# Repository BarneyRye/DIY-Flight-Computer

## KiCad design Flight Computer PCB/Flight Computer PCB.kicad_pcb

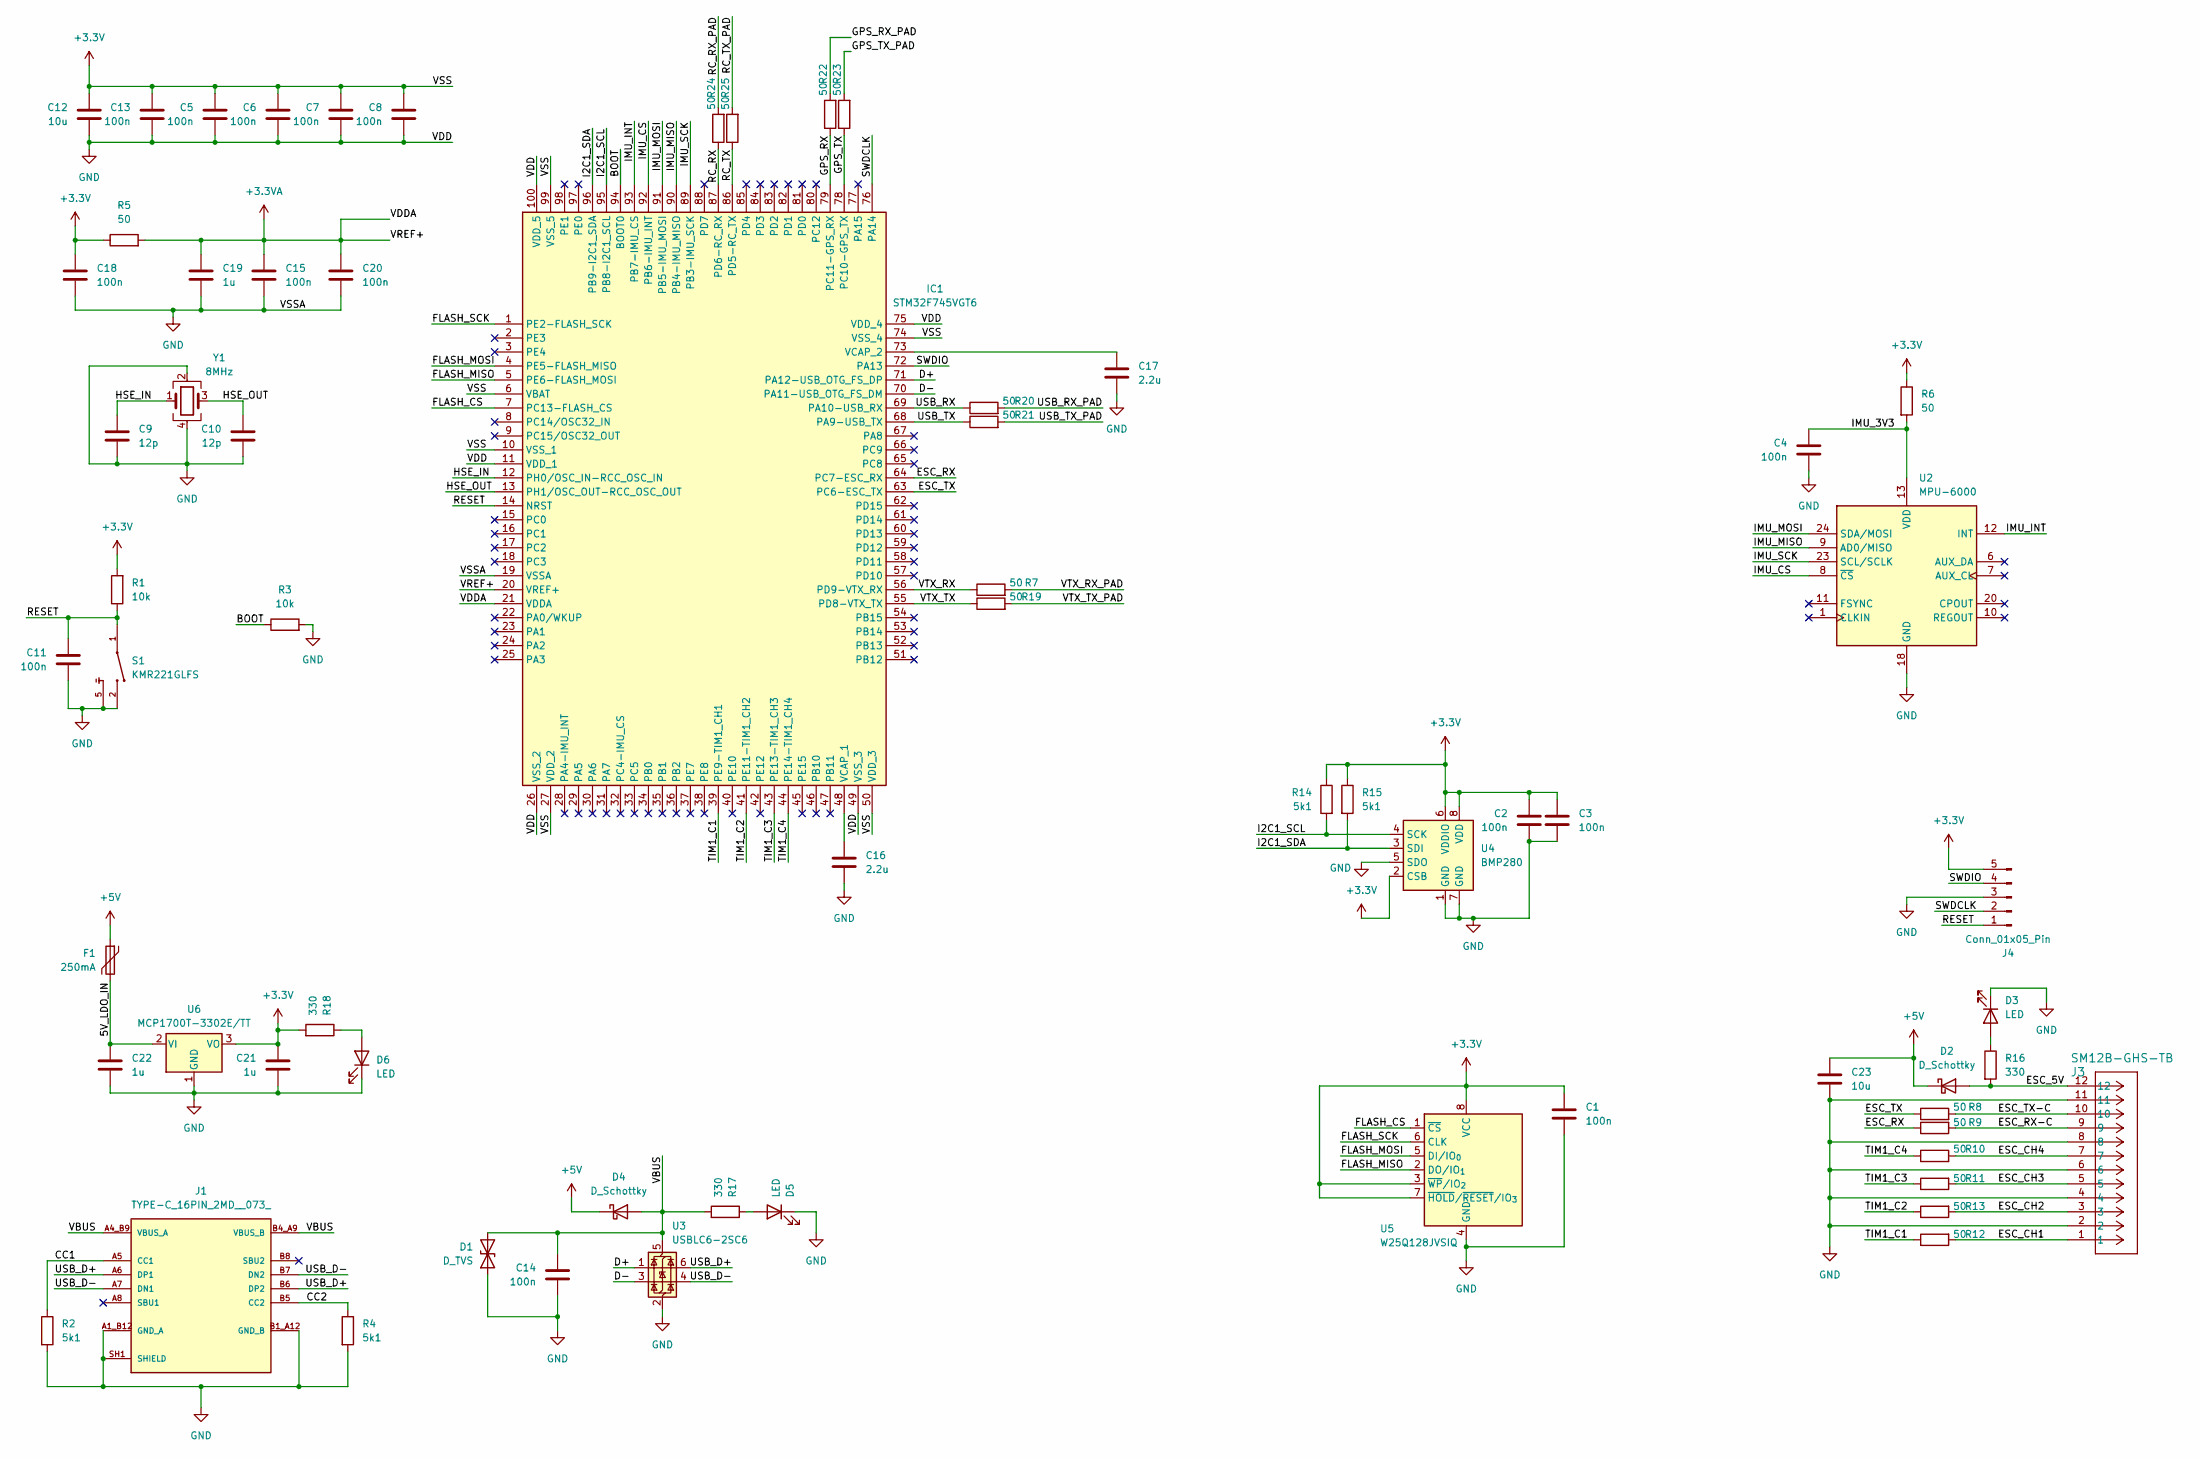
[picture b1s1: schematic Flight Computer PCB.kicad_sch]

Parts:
C1, C2, C3, C4, C5, C6, C7, C8, C11, C13, C14, C15, C18, C20: 100n; C_0805_2012Metric
C9, C10: 12p; C_0805_2012Metric
C12, C23: 10u; C_0805_2012Metric
C16, C17: 2.2u; C_0805_2012Metric
C19, C21, C22: 1u; C_0805_2012Metric
D1: D_TVS; C_0805_2012Metric
D2, D4: D_Schottky; C_0805_2012Metric
D3, D5, D6: LED; LED_0805_2012Metric
F1: 250mA; C_0805_2012Metric
IC1: STM32F745VGT6; QFP50P1600X1600X160-100N
J1: TYPE-C_16PIN_2MD__073_; SHOUHAN_TYPE-C_16PIN_2MD__073_; Part NO. C393939
J3: SM12B-GHS-TB; CONN_SM12B-GHS-TB_JST
J4: Conn_01x05_Pin; PinHeader_1x05_P2.54mm_Horizontal
R1, R3: 10k; R_0805_2012Metric
R2, R4, R14, R15: 5k1; R_0805_2012Metric
R5, R6, R7, R8, R9, R10, R11, R12, R13, R19, R20, R21, R22, R23, R24, R25: 50; R_0805_2012Metric
R16, R17, R18: 330; R_0805_2012Metric
S1: KMR221GLFS; SW_KMR221GLFS; Part NO. C72443
U2: MPU-6000; InvenSense_QFN-24_4x4mm_P0.5mm
U3: USBLC6-2SC6; SOT-23-6; Part NO. C7519
U4: BMP280; Bosch_LGA-8_2x2.5mm_P0.65mm_ClockwisePinNumbering
U5: W25Q128JVSIQ; SOIC-8_5.3x5.3mm_P1.27mm
U6: MCP1700T-3302E/TT; SOT-23
Y1: 8MHz; Crystal_SMD_3225-4Pin_3.2x2.5mm; Part NO. C70590

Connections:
+3.3V: C1.2, C2.2, C3.2, C5.1, C6.1, C7.1, C8.1, C12.1, C13.1, C18.2, C21.1, IC1.6 (VBAT), IC1.10 (VSS_1), IC1.27 (VDD_2), IC1.50 (VDD_3), IC1.74 (VSS_4), IC1.99 (VSS_5), J4.5, R1.2, R5.1, R6.1, R14.1, R15.1, R18.2, U4.2 (CSB), U4.6 (VDDIO), U4.8 (VDD), U5.3 (~WP/IO_{2}), U5.7 (~HOLD/~RESET/IO_{3}), U5.8 (VCC), U6.3 (VO)
+3.3VA: C15.2, C19.1, C20.2, IC1.20 (VREF+), IC1.21 (VDDA), R5.2
+5V: C23.1, D2.1 (K), D4.1 (K), F1.1
/5V_LDO_IN: C22.1, F1.2, U6.2 (VI)
/BOOT: IC1.94 (BOOT0), R3.1
/CC1: J1.A5 (CC1), R2.1
/CC2: J1.B5 (CC2), R4.1
/D+: IC1.71 (PA12-USB_OTG_FS_DP), U3.1 (I/O1)
/D-: IC1.70 (PA11-USB_OTG_FS_DM), U3.3 (I/O2)
/ESC_5V: D2.2 (A), J3.12, R16.2
/ESC_CH1: J3.1, R12.2
/ESC_CH2: J3.3, R13.2
/ESC_CH3: J3.5, R11.2
/ESC_CH4: J3.7, R10.2
/ESC_RX: IC1.64 (PC7-ESC_RX), R9.1
/ESC_RX-C: J3.9, R9.2
/ESC_TX: IC1.63 (PC6-ESC_TX), R8.1
/ESC_TX-C: J3.10, R8.2
/FLASH_CS: IC1.7 (PC13-FLASH_CS), U5.1 (~CS)
/FLASH_MISO: IC1.5 (PE6-FLASH_MOSI), U5.2 (DO/IO_{1})
/FLASH_MOSI: IC1.4 (PE5-FLASH_MISO), U5.5 (DI/IO_{0})
/FLASH_SCK: IC1.1 (PE2-FLASH_SCK), U5.6 (CLK)
/GPS_RX: IC1.79 (PC11-GPS_RX), R22.1
/GPS_RX_PAD: R22.2
/GPS_TX: IC1.78 (PC10-GPS_TX), R23.1
/GPS_TX_PAD: R23.2
/HSE_IN: C9.1, IC1.12 (PH0/OSC_IN-RCC_OSC_IN), Y1.1
/HSE_OUT: C10.1, IC1.13 (PH1/OSC_OUT-RCC_OSC_OUT), Y1.3
/I2C1_SCL: IC1.95 (PB8-I2C1_SCL), R14.2, U4.4 (SCK)
/I2C1_SDA: IC1.96 (PB9-I2C1_SDA), R15.2, U4.3 (SDI)
/IMU_3V3: C4.1, R6.2, U2.13 (VDD)
/IMU_CS: IC1.92 (PB6-IMU_INT), U2.8 (~CS)
/IMU_INT: IC1.93 (PB7-IMU_CS), U2.12 (INT)
/IMU_MISO: IC1.90 (PB4-IMU_MISO), U2.9 (AD0/MISO)
/IMU_MOSI: IC1.91 (PB5-IMU_MOSI), U2.24 (SDA/MOSI)
/IMU_SCK: IC1.89 (PB3-IMU_SCK), U2.23 (SCL/SCLK)
/RC_RX: IC1.87 (PD6-RC_RX), R24.1
/RC_RX_PAD: R24.2
/RC_TX: IC1.86 (PD5-RC_TX), R25.1
/RC_TX_PAD: R25.2
/RESET: C11.1, IC1.14 (NRST), J4.1, R1.1, S1.1, S1.4
/SWDCLK: IC1.76 (PA14), J4.2
/SWDIO: IC1.72 (PA13), J4.4
/TIM1_C1: IC1.39 (PE9-TIM1_CH1), R12.1
/TIM1_C2: IC1.41 (PE11-TIM1_CH2), R13.1
/TIM1_C3: IC1.43 (PE13-TIM1_CH3), R11.1
/TIM1_C4: IC1.44 (PE14-TIM1_CH4), R10.1
/USB_D+: J1.A6 (DP1), J1.B6 (DP2), U3.6 (I/O1)
/USB_D-: J1.A7 (DN1), J1.B7 (DN2), U3.4 (I/O2)
/USB_RX: IC1.69 (PA10-USB_RX), R20.1
/USB_RX_PAD: R20.2
/USB_TX: IC1.68 (PA9-USB_TX), R21.1
/USB_TX_PAD: R21.2
/VBUS: C14.1, D1.2 (A2), D4.2 (A), J1.A4_B9 (VBUS_A), J1.B4_A9 (VBUS_B), R17.2, U3.5 (VBUS)
/VTX_RX: IC1.56 (PD9-VTX_RX), R7.1
/VTX_RX_PAD: R7.2
/VTX_TX: IC1.55 (PD8-VTX_TX), R19.1
/VTX_TX_PAD: R19.2
GND: C1.1, C2.1, C3.1, C4.2, C5.2, C6.2, C7.2, C8.2, C9.2, C10.2, C11.2, C12.2, C13.2, C14.2, C15.1, C16.2, C17.1, C18.1, C19.2, C20.1, C21.2, C22.2, C23.2, D1.1 (A1), D3.1 (K), D5.1 (K), D6.1 (K), IC1.11 (VDD_1), IC1.19 (VSSA), IC1.26 (VSS_2), IC1.49 (VSS_3), IC1.75 (VDD_4), IC1.100 (VDD_5), J1.A1_B12 (GND_A), J1.B1_A12 (GND_B), J1.SH1 (SHIELD), J1.SH2 (SHIELD), J1.SH3 (SHIELD), J1.SH4 (SHIELD), J3.2, J3.4, J3.6, J3.8, J3.11, J4.3, R2.2, R3.2, R4.2, S1.2, S1.3, S1.5, U2.18 (GND), U3.2 (GND), U4.1 (GND), U4.5 (SDO), U4.7 (GND), U5.4 (GND), U6.1 (GND), Y1.2, Y1.4
unnamed: D3.2 (A), R16.1
unnamed: D5.2 (A), R17.1
unnamed: D6.2 (A), R18.1
unnamed: C16.1, IC1.48 (VCAP_1)
unnamed: C17.2, IC1.73 (VCAP_2)

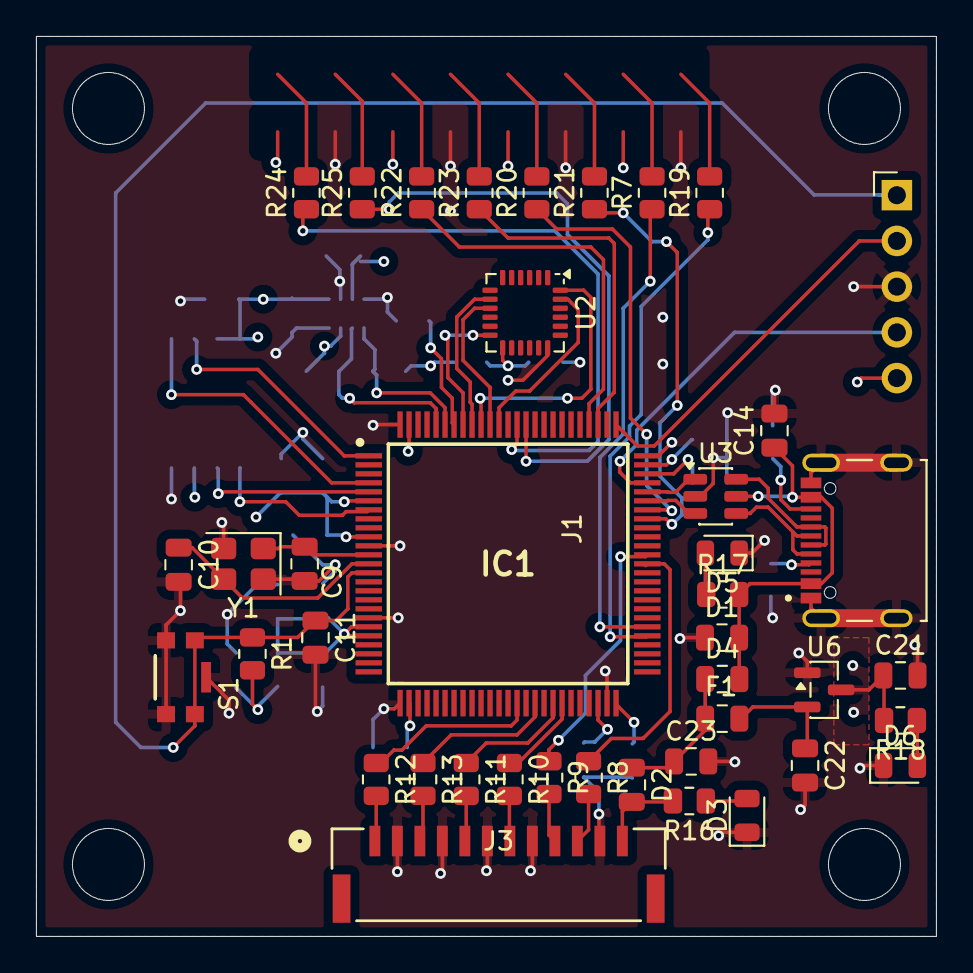
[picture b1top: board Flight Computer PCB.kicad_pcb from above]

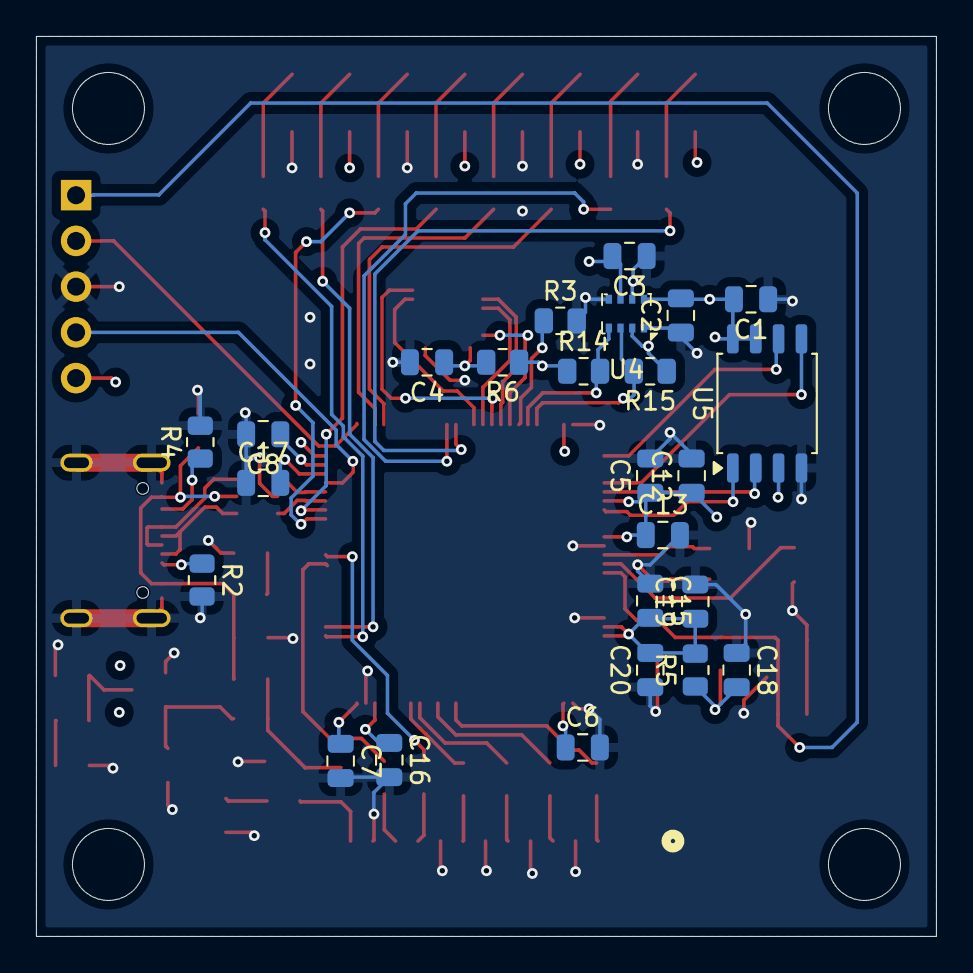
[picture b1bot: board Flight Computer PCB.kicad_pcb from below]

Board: 4 copper layers, 50.0 x 50.0 mm, 66 parts (25 on the bottom side), 56 nets.

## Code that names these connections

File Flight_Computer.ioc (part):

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Mcu.Name=STM32F745V(E-G)Tx
Mcu.Package=LQFP100
Mcu.UserName=STM32F745VGTx
PA10.GPIOParameters=GPIO_Label
PA10.GPIO_Label=USB_RX
PA10.Mode=Asynchronous
PA10.Signal=USART1_RX
PA11.Mode=Device_Only
PA11.Signal=USB_OTG_FS_DM
PA12.Mode=Device_Only
PA12.Signal=USB_OTG_FS_DP
PA4.GPIOParameters=GPIO_Label
PA4.GPIO_Label=IMU_INT
PA4.Signal=GPXTI4
PA9.GPIOParameters=GPIO_Label
PA9.GPIO_Label=USB_TX
PA9.Mode=Asynchronous
PA9.Signal=USART1_TX
PB3.GPIOParameters=GPIO_Label
PB3.GPIO_Label=IMU_SCK
PB3.Mode=Full_Duplex_Master
PB3.Signal=SPI1_SCK
PB4.GPIOParameters=GPIO_Label
PB4.GPIO_Label=IMU_MISO
PB4.Mode=Full_Duplex_Master
PB4.Signal=SPI1_MISO
PB5.GPIOParameters=GPIO_Label
PB5.GPIO_Label=IMU_MOSI
PB5.Mode=Full_Duplex_Master
PB5.Signal=SPI1_MOSI
PB6.Signal=GPIO_Output
PB7.Signal=GPXTI7
PB8.Mode=I2C
PB8.Signal=I2C1_SCL
PB9.Mode=I2C
PB9.Signal=I2C1_SDA
PC10.GPIOParameters=GPIO_Label
PC10.GPIO_Label=GPS_TX
PC10.Mode=Asynchronous
PC10.Signal=UART4_TX
PC11.GPIOParameters=GPIO_Label
PC11.GPIO_Label=GPS_RX
PC11.Mode=Asynchronous
PC11.Signal=UART4_RX
PC13.GPIOParameters=GPIO_Label
PC13.GPIO_Label=FLASH_CS
PC13.Signal=GPIO_Output
PC4.GPIOParameters=GPIO_Label
PC4.GPIO_Label=IMU_CS
PC4.Signal=GPIO_Output
PC6.GPIOParameters=GPIO_ModeDefaultPP,GPIO_Label
PC6.GPIO_Label=ESC_TX
PC6.GPIO_ModeDefaultPP=GPIO_MODE_AF_PP
PC6.Mode=Asynchronous
PC6.Signal=USART6_TX
PC7.GPIOParameters=GPIO_Label
PC7.GPIO_Label=ESC_RX
PC7.Mode=Asynchronous
PC7.Signal=USART6_RX
PD5.GPIOParameters=GPIO_Label
PD5.GPIO_Label=RC_TX
PD5.Mode=Asynchronous
PD5.Signal=USART2_TX
PD6.GPIOParameters=GPIO_Label
PD6.GPIO_Label=RC_RX
PD6.Mode=Asynchronous
PD6.Signal=USART2_RX
PD8.GPIOParameters=GPIO_Label
PD8.GPIO_Label=VTX_TX
PD8.Mode=Asynchronous
PD8.Signal=USART3_TX
PD9.GPIOParameters=GPIO_Label
PD9.GPIO_Label=VTX_RX
PD9.Mode=Asynchronous
PD9.Signal=USART3_RX
PE11.Signal=S_TIM1_CH2
PE13.Signal=S_TIM1_CH3
PE14.Signal=S_TIM1_CH4
PE2.GPIOParameters=GPIO_Label
PE2.GPIO_Label=FLASH_SCK
PE2.Mode=Full_Duplex_Master
PE2.Signal=SPI4_SCK
PE5.GPIOParameters=GPIO_Label
PE5.GPIO_Label=FLASH_MISO
PE5.Mode=Full_Duplex_Master
PE5.Signal=SPI4_MISO
PE6.GPIOParameters=GPIO_Label
PE6.GPIO_Label=FLASH_MOSI
PE6.Mode=Full_Duplex_Master
PE6.Signal=SPI4_MOSI
PE9.Signal=S_TIM1_CH1
PH0/OSC_IN.Mode=HSE-External-Oscillator
PH0/OSC_IN.Signal=RCC_OSC_IN
PH1/OSC_OUT.Mode=HSE-External-Oscillator
PH1/OSC_OUT.Signal=RCC_OSC_OUT
RCC.HSE_VALUE=8000000
RCC.SYSCLKFreq_VALUE=216000000
RCC.SYSCLKSource=RCC_SYSCLKSOURCE_PLLCLK
board=custom

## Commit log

2026-01-29 Schematic update
2026-01-29 Finished schematic
2026-01-30 Finished pcb
2026-01-30 Quick edit
2026-01-30 Added ESC.ioc
